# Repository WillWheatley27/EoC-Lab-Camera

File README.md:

| Supported Targets | ESP32 | ESP32-P4 | ESP32-S3 |
| ----------------- | ----- | -------- | -------- |

# ESP32-S3 SD + Mic + OV2640 Recorder

__WARNING:__ This project writes audio/video files to the SD card. Back up your data before testing.

Records:
- **Audio**: WAV via I2S mic (ICS-43434), `mic_0001.wav`, `mic_0002.wav`, ...
- **Video**: MJPEG via OV2640, `VID0001.MJP`, `VID0002.MJP`, ...

Core features:
- SDMMC FAT mount/unmount
- USB MSC to expose the SD card when idle
- SSD1306 I2C OLED status
- Button + buzzer UI
- BLE scan trigger (advertisements) with timestamped filenames

Supports SD (SDSC, SDHC, SDXC) cards and eMMC.

## Quick wiring map (ESP32-S3)

- **SD card:** GPIO4/5/6/7/15/16 (SDMMC)
- **Mic (I2S):** GPIO19/20/21
- **OLED (I2C):** GPIO41/42 (addr `0x3C`)
- **Camera (OV2640 SCCB):**
  - SCCB SDA: GPIO47
  - SCCB SCL: GPIO48
  - XCLK: GPIO3 (10 MHz)
  - D0..D7: GPIO8, 9, 10, 11, 12, 13, 14, 17
  - PCLK: GPIO18
  - VSYNC: GPIO21
  - HREF: GPIO46
  - PWDN/RESET: tied in hardware (PWDN → GND, RESET → 3.3V)

## Hardware

This project targets ESP32-S3 and uses an SD card breakout or slot, an I2S mic, an SSD1306 OLED, and an OV2640 camera.

Although it is possible to connect an SD card breakout adapter, keep in mind that connections using breakout cables are often unreliable and have poor signal integrity. You may need to use lower clock frequency when working with SD card breakout adapters.

This project doesn't utilize card detect (CD) and write protect (WP) signals from SD card slot.

### Pin assignments for ESP32

On ESP32, SDMMC peripheral is connected to specific GPIO pins using the IO MUX. GPIO pins cannot be customized. Please see the table below for the pin connections.

When using an ESP-WROVER-KIT board, this example runs without any extra modifications required. Only an SD card needs to be inserted into the slot.

ESP32 pin     | SD card pin | Notes
--------------|-------------|------------
GPIO14 (MTMS) | CLK         | 10k pullup in SD mode
GPIO15 (MTDO) | CMD         | 10k pullup in SD mode
GPIO2         | D0          | 10k pullup in SD mode, pull low to go into download mode (see Note about GPIO2 below!)
GPIO4         | D1          | not used in 1-line SD mode; 10k pullup in 4-line SD mode
GPIO12 (MTDI) | D2          | not used in 1-line SD mode; 10k pullup in 4-line SD mode (see Note about GPIO12 below!)
GPIO13 (MTCK) | D3          | not used in 1-line SD mode, but card's D3 pin must have a 10k pullup

### Pin assignments for ESP32-S3 (current project)

On ESP32-S3, SDMMC peripheral is connected to GPIO pins using GPIO matrix. This allows arbitrary GPIOs to be used to connect an SD card. In this example, GPIOs can be configured in two ways:

1. Using menuconfig: Run `idf.py menuconfig` in the project directory and open "SD/MMC Example Configuration" menu.
2. In the source code: See the initialization of `sdmmc_slot_config_t slot_config` structure in the example code.

The table below lists the default pin assignments.

When using an ESP32-S3-USB-OTG board, this example runs without any extra modifications required. Only an SD card needs to be inserted into the slot.

ESP32-S3 pin  | SD card pin | Notes
--------------|-------------|------------
GPIO4         | CLK         | 10k pullup
GPIO5         | CMD         | 10k pullup
GPIO6         | D0          | 10k pullup
GPIO7         | D1          | 10k pullup
GPIO15        | D2          | 10k pullup
GPIO16        | D3          | 10k pullup (required even in 1-line mode)

### I2S mic (ICS-43434)

ESP32-S3 pin  | Mic pin
--------------|---------
GPIO19        | BCLK/SCK
GPIO20        | WS/LRCL
GPIO21        | DOUT/SD
3.3V          | VCC
GND           | GND

SEL/LR on the mic should be tied to GND (left channel), which matches the code.

### OLED (SSD1306, I2C)

ESP32-S3 pin  | OLED pin
--------------|---------
GPIO41        | SDA
GPIO42        | SCL
3.3V          | VCC
GND           | GND

I2C address is `0x3C`.
Note: On ESP32-S3-DevKitC-1, GPIO41/42 are JTAG pins. Disable JTAG in `idf.py menuconfig` so they can be used for I2C.

### Camera (OV2640, Waveshare) — read this first

This project uses OV2640 over SCCB (I2C). The camera is sensitive to pin choice and initial frames are often corrupted.

**Working pin map (ESP32-S3):**

ESP32-S3 pin | OV2640 pin | Notes
-------------|------------|------
GPIO47       | SCCB SDA   | Camera I2C data
GPIO48       | SCCB SCL   | Camera I2C clock
GPIO3        | XCLK       | External clock (10 MHz)
GPIO8        | D0         | Data bit 0
GPIO9        | D1         | Data bit 1
GPIO10       | D2         | Data bit 2
GPIO11       | D3         | Data bit 3
GPIO12       | D4         | Data bit 4
GPIO13       | D5         | Data bit 5
GPIO14       | D6         | Data bit 6
GPIO17       | D7         | Data bit 7
GPIO18       | PCLK       | Pixel clock
GPIO21       | VSYNC      | Frame sync
GPIO46       | HREF       | Line sync

PWDN and RESET are tied in hardware (PWDN -> GND, RESET -> 3.3V). In software, they are disabled (set to `-1`).

**What was broken and how it was fixed:**

- SCCB was originally on GPIO36/37, which are used internally by Octal flash/PSRAM on ESP32-S3-WROOM-2, so SCCB traffic failed.
  Fix: move SCCB to GPIO47/48 and set `sccb_i2c_port = I2C_NUM_0`.
- OLED and camera shared an I2C bus, and we mixed old I2C driver with a driver_ng wrapper, causing a runtime abort.
  Fix: split buses (OLED on I2C1 GPIO41/42, camera SCCB on I2C0 GPIO47/48) and remove SCCB mutex usage.
- Early frames were corrupted (NO-SOI/NO-EOI) and were written to file.
  Fix: discard the first 10 frames after init and only write frames with valid SOI/EOI markers.
- FATFS without LFN rejected long filenames.
  Fix: use 8.3 filename `VID0001.MJP`.
- OLED writes could overlap between tasks and hang I2C.
  Fix: serialize OLED I2C writes with a mutex and remove SD warning OLED spam.

**Playback note:** `VIDxxxx.MJP` is a raw MJPEG stream (not a container). VLC can play it; for QuickTime, convert to AVI/MP4.

### BLE trigger and timestamped filenames

The device scans BLE advertisements and uses a UUID-encoded timestamp to name files:

- **Video:** `MMDDHHMM.MJP`
- **Audio:** `MMDDHHMM.WAV`

If no valid BLE timestamp is seen, it falls back to the index names:

- `VID0001.MJP`
- `mic_0001.wav`

**UUID format (128-bit):** `00000000-0000-0000-TT00-YYMMDDHHMMSS`

- Prefix is fixed: all zeroes (`00 00 00 00 00 00 00 00`)
- `TT` = `01` short press, `02` long press
- `YYMMDDHHMMSS` are BCD digits (base-10 nibbles)
- Filenames use `MMDDHHMM` to stay 8.3-safe

### Button + buzzer

ESP32-S3 pin  | Device
--------------|---------
GPIO1         | Button (pull-up input)
GPIO2         | Passive buzzer (PWM output)

### Pin assignments for ESP32-P4

On ESP32-P4, Slot 1 of the SDMMC peripheral is connected to GPIO pins using GPIO matrix. This allows arbitrary GPIOs to be used to connect an SD card. In this example, GPIOs can be configured in two ways:

1. Using menuconfig: Run `idf.py menuconfig` in the project directory and open `SD/MMC Example Configuration` menu.
2. In the source code: See the initialization of `sdmmc_slot_config_t slot_config` structure in the example code.

The table below lists the default pin assignments.

ESP32-P4 pin  | SD card pin | Notes
--------------|-------------|------------
GPIO43        | CLK         | 10k pullup
GPIO44        | CMD         | 10k pullup
GPIO39        | D0          | 10k pullup
GPIO40        | D1          | not used in 1-line SD mode; 10k pullup in 4-line mode
GPIO41        | D2          | not used in 1-line SD mode; 10k pullup in 4-line mode
GPIO42        | D3          | not used in 1-line SD mode, but card's D3 pin must have a 10k pullup

Default dedicated pins on ESP32-P4 are able to connect to an ultra high-speed SD card (UHS-I) which requires 1.8V switching (instead of the regular 3.3V). This means the user has to provide an external LDO power supply to use them, or to enable and configure an internal LDO via `idf.py menuconfig` -> `SD/MMC Example Configuration` -> `SD power supply comes from internal LDO IO`.

When using different GPIO pins this is not required and `SD power supply comes from internal LDO IO` setting can be disabled.

### 4-line and 1-line SD modes

By default, this example uses 4 line SD mode, utilizing 6 pins: CLK, CMD, D0 - D3. It is possible to use 1-line mode (CLK, CMD, D0) by changing "SD/MMC bus width" in the example configuration menu (see `CONFIG_EXAMPLE_SDMMC_BUS_WIDTH_1`).

Note that even if card's D3 line is not connected to the ESP chip, it still has to be pulled up, otherwise the card will go into SPI protocol mode.

### Note about GPIO2 (ESP32 only)

GPIO2 pin is used as a bootstrapping pin, and should be low to enter UART download mode. One way to do this is to connect GPIO0 and GPIO2 using a jumper, and then the auto-reset circuit on most development boards will pull GPIO2 low along with GPIO0, when entering download mode.

- Some boards have pulldown and/or LED on GPIO2. LED is usually ok, but pulldown will interfere with D0 signals and must be removed. Check the schematic of your development board for anything connected to GPIO2.

### Note about GPIO12 (ESP32 only)

GPIO12 is used as a bootstrapping pin to select output voltage of an internal regulator which powers the flash chip (VDD_SDIO). This pin has an internal pulldown so if left unconnected it will read low at reset (selecting default 3.3V operation). When adding a pullup to this pin for SD card operation, consider the following:

- For boards which don't use the internal regulator (VDD_SDIO) to power the flash, GPIO12 can be pulled high.
- For boards which use 1.8V flash chip, GPIO12 needs to be pulled high at reset. This is fully compatible with SD card operation.
- On boards which use the internal regulator and a 3.3V flash chip, GPIO12 must be low at reset. This is incompatible with SD card operation.
    * In most cases, external pullup can be omitted and an internal pullup can be enabled using a `gpio_pullup_en(GPIO_NUM_12);` call. Most SD cards work fine when an internal pullup on GPIO12 line is enabled. Note that if ESP32 experiences a power-on reset while the SD card is sending data, high level on GPIO12 can be latched into the bootstrapping register, and ESP32 will enter a boot loop until external reset with correct GPIO12 level is applied.
    * Another option is to burn the flash voltage selection efuses. This will permanently select 3.3V output voltage for the internal regulator, and GPIO12 will not be used as a bootstrapping pin. Then it is safe to connect a pullup resistor to GPIO12. This option is suggested for production use.

The following command can be used to program flash voltage selection efuses **to 3.3V**:

```sh
    espefuse.py set_flash_voltage 3.3V
```

This command will burn the `XPD_SDIO_TIEH`, `XPD_SDIO_FORCE`, and `XPD_SDIO_REG` efuses. With all three burned to value 1, the internal VDD_SDIO flash voltage regulator is permanently enabled at 3.3V. See the technical reference manual for more details.

`espefuse.py` has a `--do-not-confirm` option if running from an automated flashing script.

See [the document about pullup requirements](https://docs.espressif.com/projects/esp-idf/en/latest/api-reference/peripherals/sd_pullup_requirements.html) for more details about pullup support and compatibility of modules and development boards.

## How to use

### Build and flash

Build the project and flash it to the board, then run monitor tool to view serial output:

```
idf.py -p PORT flash monitor
```

(Replace PORT with serial port name.)

(To exit the serial monitor, type ``Ctrl-]``.)

### Recording flow

1. Long press starts recording. USB MSC is stopped and the SD card is mounted to the app.
2. Audio is written to `mic_0001.wav`, `mic_0002.wav`, etc.
3. Long press again stops recording, finalizes the WAV header, and returns the SD card to USB MSC.
4. A later long press repeats the cycle with a new filename.

Short press toggles pause/resume during recording. Each press produces a short beep.

### SD card mount warnings

If SD mounting fails or is not ready, the OLED shows a warning:

- `SD init failed`
- `SD mount failed`
- `SD not ready`

When these appear, re-seat the SD card and try again. Also wait for the
`Exposing SD card over USB` log before unplugging or copying files.

See the Getting Started Guide for full steps to configure and use ESP-IDF to build projects.

### USB mass storage

When idle, the SD card is exposed over USB MSC for file access from your computer.
During recording, USB MSC is stopped and the SD card is mounted to the application.
After recording finishes, USB MSC is restarted and the card is visible again on the host.

## Example output

Here is an example console output. In this case a 128MB SDSC card was connected, and `EXAMPLE_FORMAT_IF_MOUNT_FAILED` menuconfig option enabled. Card was unformatted, so the initial mount has failed. Card was then partitioned, formatted, and mounted again.

```
I (336) example: Initializing SD card
I (336) example: Using SDMMC peripheral
I (420) example: Mounting filesystem
I (538) mic: Waiting for long press
I (1840) button: Recording started
I (1841) mic: Recording started
I (9620) mic: Stop requested
I (9622) mic: Captured 7 sec to /sdcard/mic_0001.wav
I (9660) example: Card unmounted
```

## Troubleshooting

### Failure to download the example

```
Connecting........_____....._____....._____....._____....._____....._____....._____

A fatal error occurred: Failed to connect to Espressif device: Invalid head of packet (0x34)
```

Disconnect the SD card D0/MISO line from GPIO2 and try uploading again. Read "Note about GPIO2" above.

### Card fails to initialize with `sdmmc_init_sd_scr: send_scr (1) returned 0x107` error

Check connections between the card and the ESP32. For example, if you have disconnected GPIO2 to work around the flashing issue, connect it back and reset the ESP32 (using a button on the development board, or by pressing Ctrl-T Ctrl-R in IDF Monitor).

### Card fails to initialize with `sdmmc_check_scr: send_scr returned 0xffffffff` error

Connections between the card and the ESP32 are too long for the frequency used. Try using shorter connections, or try reducing the clock speed of SD interface.

### Failure to mount filesystem

```
example: Failed to mount filesystem. If you want the card to be formatted, set the EXAMPLE_FORMAT_IF_MOUNT_FAILED menuconfig option.
```
The example will be able to mount only cards formatted using FAT32 filesystem. If the card is formatted as exFAT or some other filesystem, you have an option to format it in the example code. Enable the `EXAMPLE_FORMAT_IF_MOUNT_FAILED` menuconfig option, then build and flash the example.

### Debug SD connections and pullup strength

> If the initialization of the SD card fails, initially follow the above options. If the issue persists, confirm the connection of pullups to the SD pins. To do this, enable the` Debug sd pin connections and pullup strength` option from menuconfig and rerun the code. This will provide the following result:

```
**** PIN recovery time ****

PIN 14 CLK  10044 cycles
PIN 15 CMD  10034 cycles
PIN  2  D0  10034 cycles
PIN  4  D1  10034 cycles
PIN 12  D2  10034 cycles
PIN 13  D3  10034 cycles

**** PIN recovery time with weak pullup ****

PIN 14 CLK  100 cycles
PIN 15 CMD  100 cycles
PIN  2  D0  100 cycles
PIN  4  D1  100 cycles
PIN 12  D2  100 cycles
PIN 13  D3  100 cycles

**** PIN voltage levels ****

PIN 14 CLK  0.6V
PIN 15 CMD  0.3V
PIN  2  D0  0.8V
PIN  4  D1  0.6V
PIN 12  D2  0.4V
PIN 13  D3  0.8V

**** PIN voltage levels with weak pullup ****

PIN 14 CLK  1.0V
PIN 15 CMD  1.1V
PIN  2  D0  1.0V
PIN  4  D1  1.0V
PIN 12  D2  1.0V
PIN 13  D3  1.2V

**** PIN cross-talk ****

              CLK   CMD    D0    D1    D2    D3
PIN 14 CLK     --   0.2V  0.1V  0.1V  0.1V  0.2V
PIN 15 CMD    0.1V   --   0.1V  0.1V  0.1V  0.1V
PIN  2  D0    0.1V  0.1V   --   0.2V  0.1V  0.1V
PIN  4  D1    0.1V  0.1V  0.3V   --   0.1V  0.1V
PIN 12  D2    0.1V  0.2V  0.2V  0.1V   --   0.1V
PIN 13  D3    0.1V  0.2V  0.1V  0.1V  0.1V   --

**** PIN cross-talk with weak pullup ****

              CLK   CMD    D0    D1    D2    D3
PIN 14 CLK     --   1.0V  1.0V  1.0V  1.0V  1.2V
PIN 15 CMD    0.9V   --   1.0V  1.0V  1.0V  1.2V
PIN  2  D0    0.9V  1.0V   --   1.0V  1.0V  1.2V
PIN  4  D1    0.9V  1.0V  1.2V   --   1.0V  1.2V
PIN 12  D2    0.9V  1.1V  1.2V  0.9V   --   1.2V
PIN 13  D3    0.9V  1.2V  1.1V  0.9V  0.9V   --
I (845) main_task: Returned from app_main()
```

In the absence of connected pullups and having the weak pullups enabled, you can assess the pullup connections by comparing PIN recovery time measured in CPU cycles. To check pullup connections, configure the pin as open drain, set it to low state, and count the cpu cycles consumed before returning to high state. If a pullup is connected, the pin will get back to high state after reasonably small cycle count, typically around 50-300 cycles, depending on pullup strength. If no pullup is connected, the PIN stays low and the measurement times out after 10000 cycles.

It will also provide the voltage levels at the corresponding SD pins. By default, this information is provided for ESP32 chip only, and for other chipsets, verify the availability of ADC pins for the respective GPIO using [this](https://docs.espressif.com/projects/esp-idf/en/latest/esp32/api-reference/peripherals/gpio.html#gpio-summary) and configure ADC mapped pins using menuconfig. Then test the voltage levels accordingly.

You can monitor the voltage levels of individual pins using `PIN voltage levels` and `PIN voltage levels with weak pullup`. However, if one pin being pulled low and experiencing interference with another pin, you can detect it through `PIN cross-talk` and `PIN cross-talk with weak pullup`. In the absence of pullups, voltage levels at each pin should range from 0 to 0.3V. With 10k pullups connected, the voltage will be between 3.1V to 3.3V, contingent on the connection between ADC pins and SD pins, and with weak pullups connected, it can fluctuate between 0.8V to 1.2V, depending on pullup strength.
>>>>>>> 207d2c1 (Initial commit)

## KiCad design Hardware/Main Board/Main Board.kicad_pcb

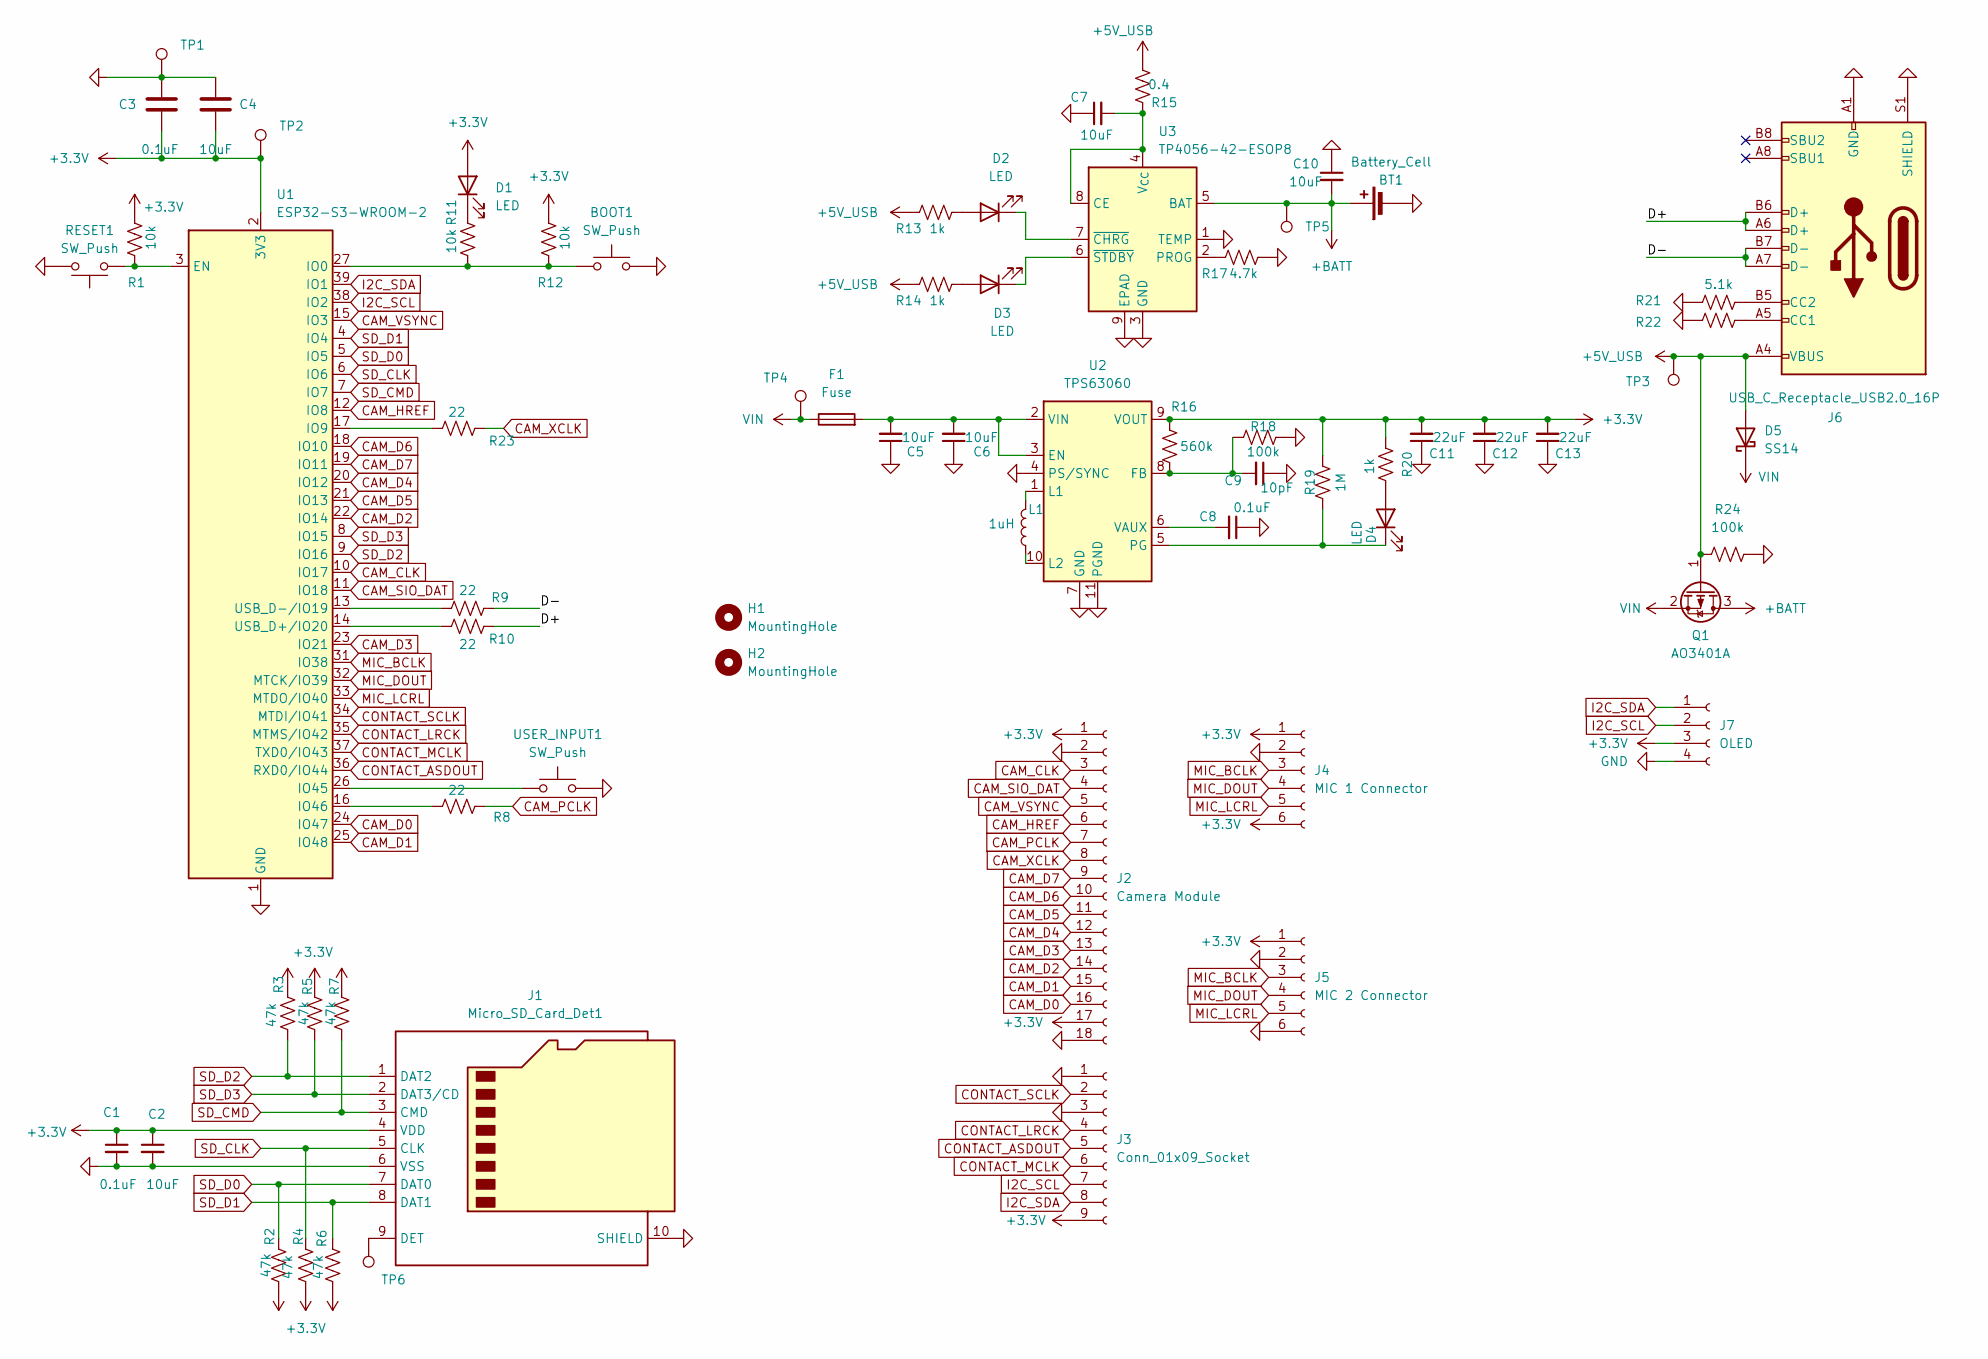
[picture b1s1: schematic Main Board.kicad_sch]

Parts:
BOOT1: SW_Push; SW_SPST_EVQP7A
BT1: Battery_Cell; JST_GH_SM02B-GHS-TB_1x02-1MP_P1.25mm_Horizontal
C1, C3, C8: 0.1uF; C_0402_1005Metric
C2, C7, C10: 10uF; C_0402_1005Metric
C4, C5, C6: 10uF; C_0603_1608Metric
C9: 10pF; C_0402_1005Metric
C11, C12, C13: 22uF; C_0805_2012Metric
D1, D2, D3, D4: LED; LED_0603_1608Metric
D5: SS14; D_SMA
F1: Fuse; Fuse_1206_3216Metric
H1, H2: MountingHole; MountingHole_2.1mm
J1: Micro_SD_Card_Det1; microSD_HC_Molex_104031-0811
J2: Camera Module; PinHeader_2x09_P2.54mm_Vertical
J3: Conn_01x09_Socket; JST_GH_SM09B-GHS-TB_1x09-1MP_P1.25mm_Horizontal
J4: MIC 1 Connector; JST_GH_SM06B-GHS-TB_1x06-1MP_P1.25mm_Horizontal
J5: MIC 2 Connector; JST_GH_SM06B-GHS-TB_1x06-1MP_P1.25mm_Horizontal
J6: USB_C_Receptacle_USB2.0_16P; USB_C_Receptacle_HRO_TYPE-C-31-M-12
J7: OLED; PinHeader_1x04_P2.54mm_Vertical
L1: 1uH; L_Bourns-SRN4018
Q1: AO3401A; SOT-23
R1, R11, R12: 10k; R_0402_1005Metric
R2, R3, R4, R5, R6, R7: 47k; R_0402_1005Metric
R8, R9, R10, R23: 22; R_0402_1005Metric
R13, R14, R20: 1k; R_0402_1005Metric
R15: 0.4; R_0402_1005Metric
R16: 560k; R_0402_1005Metric
R17: 4.7k; R_0402_1005Metric
R18, R24: 100k; R_0402_1005Metric
R19: 1M; R_0402_1005Metric
R21, R22: 5.1k; R_0402_1005Metric
RESET1: SW_Push; SW_SPST_EVQP7A
TP1, TP2, TP3: TestPoint; PinHeader_1x01_P2.54mm_Vertical
TP4, TP5, TP6: TestPoint; TestPoint_Pad_1.0x1.0mm
U1: ESP32-S3-WROOM-2
U2: TPS63060; Texas_S-PWSON-N10_ThermalVias
U3: TP4056-42-ESOP8; SOIC-8-1EP_3.9x4.9mm_P1.27mm_EP2.41x3.3mm_ThermalVias
USER_INPUT1: SW_Push; SW_SPST_PTS645

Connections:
+3.3V: C1.1, C2.1, C3.2, C4.1, C11.2, C12.2, C13.2, D1.2 (A), J1.4 (VDD), J2.1, J2.17, J3.9, J4.1, J4.6, J5.1, J7.3, R1.1, R2.1, R3.2, R4.1, R5.2, R6.1, R7.2, R12.1, R16.2, R19.2, R20.2, TP2.1, U1.2 (3V3), U2.9 (VOUT)
+5V_USB: D5.2 (A), J6.A4 (VBUS), J6.A9 (VBUS), J6.B4 (VBUS), J6.B9 (VBUS), Q1.1 (G), R13.2, R14.2, R15.1, R24.1, TP3.1
+BATT: BT1.1 (+), C10.2, Q1.3 (D), TP5.1, U3.5 (BAT)
/D+: J6.A6 (D+), J6.B6 (D+), R10.1
/D-: J6.A7 (D-), J6.B7 (D-), R9.1
CAM_CLK: J2.3, U1.10 (IO17)
CAM_D0: J2.16, U1.24 (IO47)
CAM_D1: J2.15, U1.25 (IO48)
CAM_D2: J2.14, U1.22 (IO14)
CAM_D3: J2.13, U1.23 (IO21)
CAM_D4: J2.12, U1.20 (IO12)
CAM_D5: J2.11, U1.21 (IO13)
CAM_D6: J2.10, U1.18 (IO10)
CAM_D7: J2.9, U1.19 (IO11)
CAM_HREF: J2.6, U1.12 (IO8)
CAM_PCLK: J2.7, R8.2
CAM_SIO_DAT: J2.4, U1.11 (IO18)
CAM_VSYNC: J2.5, U1.15 (IO3)
CAM_XCLK: J2.8, R23.2
CONTACT_ASDOUT: J3.5, U1.36 (RXD0/IO44)
CONTACT_LRCK: J3.4, U1.35 (MTMS/IO42)
CONTACT_MCLK: J3.6, U1.37 (TXD0/IO43)
CONTACT_SCLK: J3.2, U1.34 (MTDI/IO41)
GND: BOOT1.2, BT1.2 (-), C1.2, C2.2, C3.1, C4.2, C5.1, C6.1, C7.1, C8.1, C9.1, C10.1, C11.1, C12.1, C13.1, J1.6 (VSS), J1.10 (SHIELD), J2.2, J2.18, J3.1, J3.3, J4.2, J5.2, J5.6, J6.A1 (GND), J6.A12 (GND), J6.B1 (GND), J6.B12 (GND), J6.S1 (SHIELD), J7.4, R17.1, R18.1, R21.2, R22.2, R24.2, RESET1.2, TP1.1, U1.1 (GND), U1.40 (GND), U1.41 (GND), U2.4 (PS/SYNC), U2.7 (GND), U2.11 (PGND), U3.1 (TEMP), U3.3 (GND), U3.9 (EPAD), USER_INPUT1.2
I2C_SCL: J3.7, J7.2, U1.38 (IO2)
I2C_SDA: J3.8, J7.1, U1.39 (IO1)
MIC_BCLK: J4.3, J5.3, U1.31 (IO38)
MIC_DOUT: J4.4, J5.4, U1.32 (MTCK/IO39)
MIC_LCRL: J4.5, J5.5, U1.33 (MTDO/IO40)
unnamed: D1.1 (K), R11.2
unnamed: D2.2 (A), R13.1
unnamed: D2.1 (K), U3.7 (~CHRG)
unnamed: D3.2 (A), R14.1
unnamed: D3.1 (K), U3.6 (~STDBY)
unnamed: D4.2 (A), R20.1
unnamed: D4.1 (K), R19.1, U2.5 (PG)
unnamed: J1.9 (DET), TP6.1
unnamed: J6.A5 (CC1), R22.1
unnamed: J6.B5 (CC2), R21.1
unnamed: R1.2, RESET1.1, U1.3 (EN)
unnamed: BOOT1.1, R11.1, R12.2, U1.27 (IO0)
unnamed: R23.1, U1.17 (IO9)
unnamed: U1.26 (IO45), USER_INPUT1.1
unnamed: R8.1, U1.16 (IO46)
unnamed: R10.2, U1.14 (USB_D+/IO20)
unnamed: R9.2, U1.13 (USB_D-/IO19)
unnamed: C5.2, C6.2, F1.2, U2.2 (VIN), U2.3 (EN)
unnamed: C9.2, R16.1, R18.2, U2.8 (FB)
unnamed: L1.2, U2.1 (L1)
unnamed: L1.1, U2.10 (L2)
unnamed: C8.2, U2.6 (VAUX)
unnamed: C7.2, R15.2, U3.4 (V_{CC}), U3.8 (CE)
unnamed: R17.2, U3.2 (PROG)
SD_CLK: J1.5 (CLK), R4.2, U1.6 (IO6)
SD_CMD: J1.3 (CMD), R7.1, U1.7 (IO7)
SD_D0: J1.7 (DAT0), R2.2, U1.5 (IO5)
SD_D1: J1.8 (DAT1), R6.2, U1.4 (IO4)
SD_D2: J1.1 (DAT2), R3.1, U1.9 (IO16)
SD_D3: J1.2 (DAT3/CD), R5.1, U1.8 (IO15)
VIN: D5.1 (K), F1.1, Q1.2 (S), TP4.1

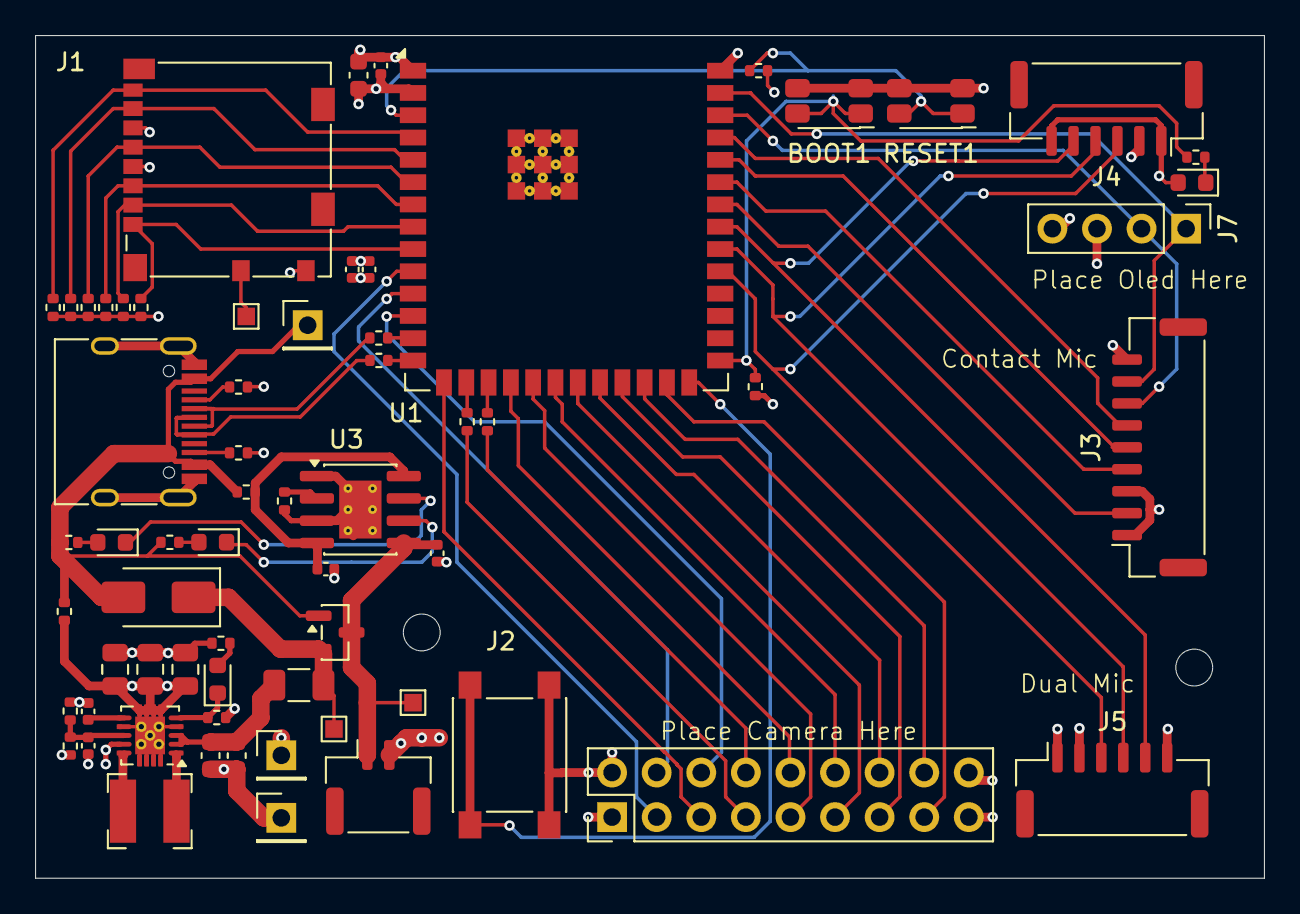
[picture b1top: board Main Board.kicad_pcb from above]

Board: 4 copper layers, 70.0 x 48.0 mm, 67 parts (0 on the bottom side), 60 nets.

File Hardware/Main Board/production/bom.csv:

Designator,Footprint,Quantity,Value,LCSC Part #
"BOOT1, RESET1",SW_SPST_EVQP7A,2,SW_Push,
BT1,JST_GH_SM02B-GHS-TB_1x02-1MP_P1.25mm_Horizontal,1,Battery_Cell,
"C1, C3, C8",0402,3,0.1uF,
"C10, C2, C7",0402,3,10uF,
"C11, C12, C13",0805,3,22uF,
"C4, C5, C6",0603,3,10uF,
C9,0402,1,10pF,
"D1, D2, D3, D4",0603,4,LED,
D5,D_SMA,1,SS14,
F1,1206,1,Fuse,
J1,microSD_HC_Molex_104031-0811,1,Micro_SD_Card_Det1,
J2,PinHeader_2x09_P2.54mm_Vertical,1,Camera Module,
J3,JST_GH_SM09B-GHS-TB_1x09-1MP_P1.25mm_Horizontal,1,Conn_01x09_Socket,
J4,JST_GH_SM06B-GHS-TB_1x06-1MP_P1.25mm_Horizontal,1,MIC 1 Connector,
J5,JST_GH_SM06B-GHS-TB_1x06-1MP_P1.25mm_Horizontal,1,MIC 2 Connector,
J6,USB_C_Receptacle_HRO_TYPE-C-31-M-12,1,USB_C_Receptacle_USB2.0_16P,
J7,PinHeader_1x04_P2.54mm_Vertical,1,OLED,
L1,L_Bourns-SRN4018,1,1uH,
Q1,SOT-23,1,AO3401A,
"R1, R11, R12",0402,3,10k,
"R10, R23, R8, R9",0402,4,22,
"R13, R14, R20",0402,3,1k,
R15,0402,1,0.4,
R16,0402,1,560k,
R17,0402,1,4.7k,
"R18, R24",0402,2,100k,
R19,0402,1,1M,
"R2, R3, R4, R5, R6, R7",0402,6,47k,
"R21, R22",0402,2,5.1k,
"TP1, TP2, TP3",PinHeader_1x01_P2.54mm_Vertical,3,TestPoint,
"TP4, TP5, TP6",TestPoint_Pad_1.0x1.0mm,3,TestPoint,
U1,ESP32-S3-WROOM-2,1,ESP32-S3-WROOM-2,
U2,Texas_S-PWSON-N10_ThermalVias,1,TPS63060,
U3,SOIC-8-1EP_3.9x4.9mm_P1.27mm_EP2.41x3.3mm_ThermalVias,1,TP4056-42-ESOP8,
USER_INPUT1,SW_SPST_PTS645,1,SW_Push,

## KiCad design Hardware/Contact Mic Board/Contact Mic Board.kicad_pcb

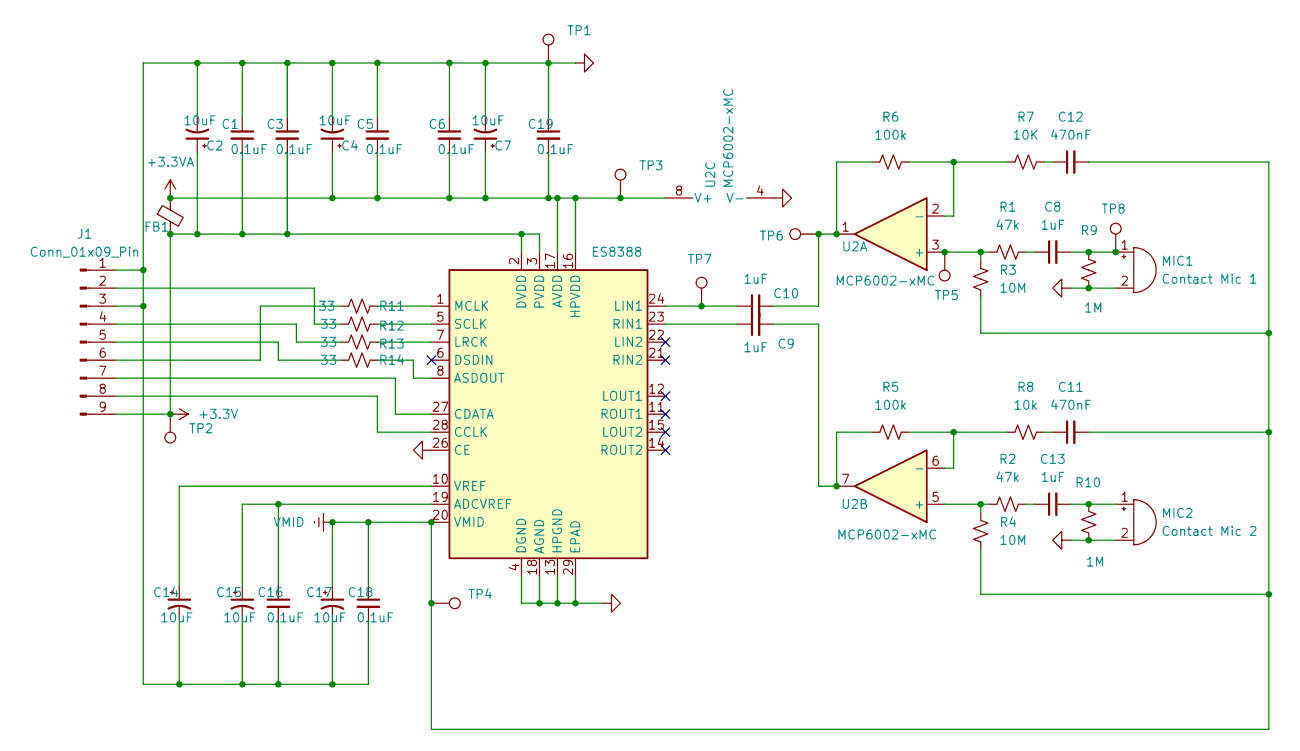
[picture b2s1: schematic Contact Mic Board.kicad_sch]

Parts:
C1, C3, C5, C6, C16, C18, C19: 0.1uF; C_0402_1005Metric
C2, C4, C7, C14, C15, C17: 10uF; C_0402_1005Metric
C8, C9, C10, C13: 1uF; C_0402_1005Metric
C11, C12: 470nF; C_0402_1005Metric
FB1: FerriteBead_Small; C_0603_1608Metric
J1: Conn_01x09_Pin; JST_GH_SM09B-GHS-TB_1x09-1MP_P1.25mm_Horizontal
MIC1: Contact Mic 1; PinHeader_1x02_P2.54mm_Vertical
MIC2: Contact Mic 2; PinHeader_1x02_P2.54mm_Vertical
R1, R2: 47k; C_0402_1005Metric
R3, R4: 10M; C_0402_1005Metric
R5, R6: 100k; D_0805_2012Metric_Pad1.15x1.40mm_HandSolder
R7: 10K; C_0402_1005Metric
R8: 10k; C_0402_1005Metric
R9, R10: 1M; C_0402_1005Metric
R11, R12, R13, R14: 33; C_0402_1005Metric
TP1, TP2, TP3, TP4, TP5, TP6, TP7, TP8: TestPoint; TestPoint_Pad_1.0x1.0mm
U1: ES8388; QFN-28-1EP_4x4mm_P0.45mm_EP2.6x2.6mm
U2: MCP6002-xMC; DFN-8-1EP_3x2mm_P0.5mm_EP1.75x1.45mm

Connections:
+3.3V: C1.2, C2.1, C3.2, FB1.2, J1.9, TP2.1, U1.2 (DVDD), U1.3 (PVDD)
+3.3VA: C4.1, C5.2, C6.2, C7.1, C19.2, FB1.1, TP3.1, U1.16 (HPVDD), U1.17 (AVDD), U2.8 (V+)
GND: C1.1, C2.2, C3.1, C4.2, C5.1, C6.1, C7.2, C14.2, C15.2, C16.2, C17.2, C18.2, C19.1, J1.1, J1.3, MIC1.2 (-), MIC2.2 (-), R9.2, R10.2, TP1.1, U1.4 (DGND), U1.13 (HPGND), U1.18 (AGND), U1.26 (CE), U1.29 (EPAD), U2.4 (V-), U2.9 (V-)
unnamed: C8.1, R1.2
unnamed: C9.2, R5.2, U2.7
unnamed: C10.2, R6.1, TP6.1, U2.1
unnamed: C11.1, R8.2
unnamed: C12.1, R7.2
unnamed: C13.1, R2.2
unnamed: J1.2, R12.1
unnamed: J1.4, R13.1
unnamed: J1.5, R14.1
unnamed: J1.6, R11.1
unnamed: J1.7, U1.27 (CDATA)
unnamed: J1.8, U1.28 (CCLK)
unnamed: C8.2, MIC1.1 (+), R9.1, TP8.1
unnamed: C13.2, MIC2.1 (+), R10.1
unnamed: C15.1, C16.1, U1.19 (ADCVREF)
unnamed: R14.2, U1.8 (ASDOUT)
unnamed: C10.1, TP7.1, U1.24 (LIN1)
unnamed: R13.2, U1.7 (LRCK)
unnamed: R11.2, U1.1 (MCLK)
unnamed: C9.1, U1.23 (RIN1)
unnamed: R12.2, U1.5 (SCLK)
unnamed: C14.1, U1.10 (VREF)
unnamed: R1.1, R3.1, TP5.1, U2.3 (+)
unnamed: R6.2, R7.1, U2.2 (-)
unnamed: R2.1, R4.1, U2.5 (+)
unnamed: R5.1, R8.1, U2.6 (-)
VMID: C11.2, C12.2, C17.1, C18.1, R3.2, R4.2, TP4.1, U1.20 (VMID)

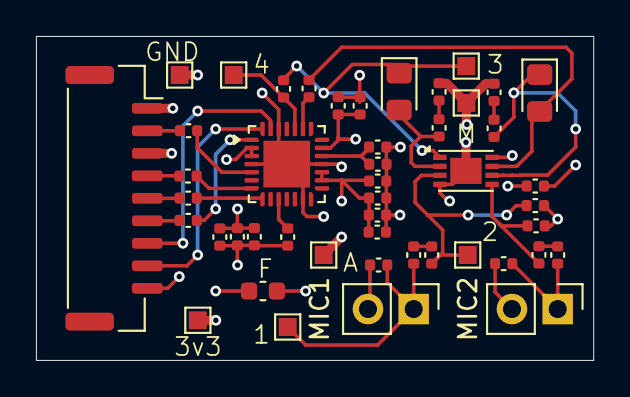
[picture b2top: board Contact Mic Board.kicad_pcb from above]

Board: 4 copper layers, 31.0 x 18.0 mm, 47 parts (0 on the bottom side), 30 nets.

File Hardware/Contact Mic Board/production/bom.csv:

Designator,Footprint,Quantity,Value,LCSC Part #
"C1, C16, C18, C19, C3, C5, C6",0402,7,0.1uF,
"C10, C13, C8, C9",0402,4,1uF,
"C11, C12",0402,2,470nF,
"C14, C15, C17, C2, C4, C7",0402,6,10uF,
FB1,0603,1,FerriteBead_Small,
J1,JST_GH_SM09B-GHS-TB_1x09-1MP_P1.25mm_Horizontal,1,Conn_01x09_Pin,
"R1, R2",0402,2,47k,
"R10, R9",0402,2,1M,
"R11, R12, R13, R14",0402,4,33,
"R3, R4",0402,2,10M,
"R5, R6",0805,2,100k,
"R7, R8",0402,2,10K,
U1,QFN-28-1EP_4x4mm_P0.45mm_EP2.6x2.6mm,1,ES8388,
U2,DFN-8-1EP_3x2mm_P0.5mm_EP1.75x1.45mm,1,MCP6002-xMC,

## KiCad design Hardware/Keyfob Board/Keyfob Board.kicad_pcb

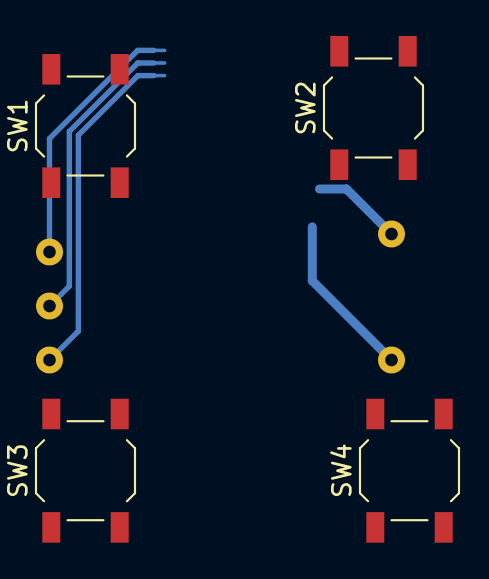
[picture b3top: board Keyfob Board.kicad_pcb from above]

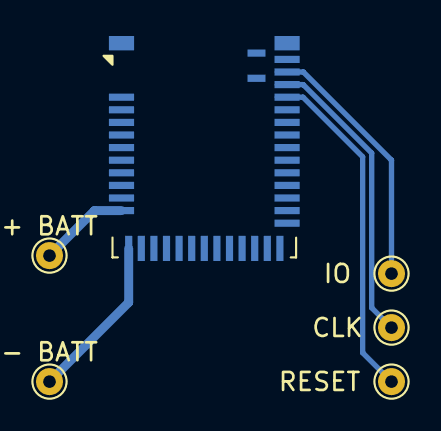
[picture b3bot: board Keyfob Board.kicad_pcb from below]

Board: 2 copper layers, 10 parts (6 on the bottom side), 9 nets.

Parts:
+ BATT: TestPoint; TestPoint_THTPad_D1.5mm_Drill0.7mm
- BATT: TestPoint; TestPoint_THTPad_D1.5mm_Drill0.7mm
CLK: TestPoint; TestPoint_THTPad_D1.5mm_Drill0.7mm
IO: TestPoint; TestPoint_THTPad_D1.5mm_Drill0.7mm
RESET: TestPoint; TestPoint_THTPad_D1.5mm_Drill0.7mm
SW1, SW2, SW3, SW4: SW_Push; SW_SPST_TL3342
U1: MDBT42Q-512K; Raytac_MDBT42Q

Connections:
+BATT: + BATT.1, U1.11 (VDD)
-BATT: - BATT.1, SW1.2, SW2.2, SW3.2, SW4.2, U1.1 (GND), U1.12 (GND), U1.24 (GND), U1.39 (GND)
unnamed: SW1.1, U1.25 (P0.11)
unnamed: SW2.1, U1.26 (P0.12)
unnamed: RESET.1, U1.35 (P0.21/~RESET)
unnamed: SW3.1, U1.40 (P0.24)
unnamed: SW4.1, U1.2 (P0.25)
unnamed: CLK.1, U1.36 (SWDCLK)
unnamed: IO.1, U1.37 (SWDIO)

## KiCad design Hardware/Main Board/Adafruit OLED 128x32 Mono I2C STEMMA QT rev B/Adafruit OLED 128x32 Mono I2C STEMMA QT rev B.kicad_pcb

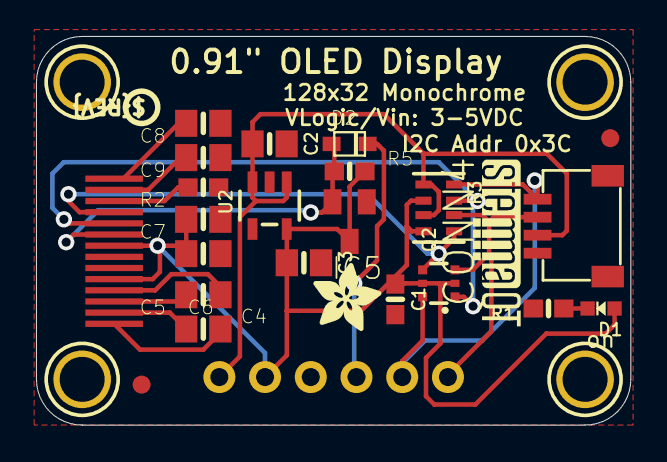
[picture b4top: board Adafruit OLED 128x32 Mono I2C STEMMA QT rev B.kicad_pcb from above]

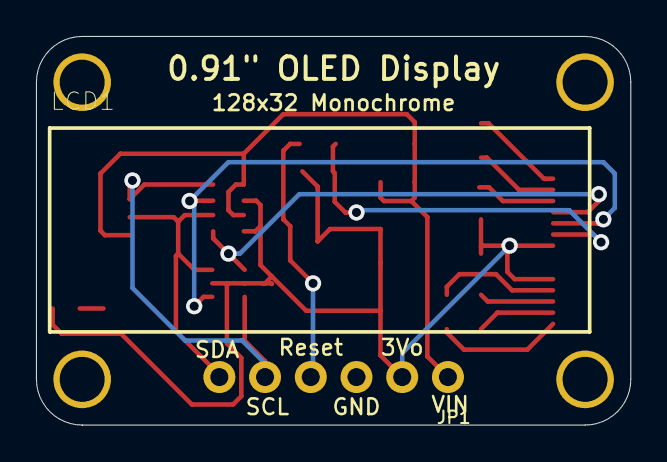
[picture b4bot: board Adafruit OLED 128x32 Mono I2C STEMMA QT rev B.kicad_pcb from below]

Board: 2 copper layers, 33.0 x 21.6 mm, 30 parts (2 on the bottom side), 17 nets.

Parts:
C1: 0.1uF; 0603-NO
C2, C3, C8, C9: 10uF; 0805-NO
C4, C5, C6, C7: 1uF; 0805-NO
CONN4: STEMMA_I2C_QT; JST_SH4
D1: GREEN; CHIPLED_0603_NOOUTLINE
D2: 1N4148; SOD-323F
FID3, FID4: FIDUCIAL_1MM
IC5: APX803; SOT23
JP1: 1X06_ROUND_70
LCD1: UG-2832HSWEG02_WRAPUNDER
Q2: BSS138; SOT363
R1, R5: 10K; 0603-NO
R2: 390K; 0603-NO
R3: 10K; RESPACK_4X0603
U2: AP2112K-3.3; SOT23-5
U$1, U$17, U$19, U$21: MOUNTINGHOLE2.5; MOUNTINGHOLE_2.5_PLATED
U$22: ADAFRUIT_3.5MM
U$25: PCBFEAT-REV-040
U$31: STEMMAQT

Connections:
3.3V: C1.1, C3.1, C6.2, C7.2, D1.A, IC5.3, JP1.2, LCD1.5, LCD1.8, Q2.2, Q2.5, R3.2, R3.4, R5.2, U2.5
GND: C1.2, C2.2, C3.2, C6.1, C7.1, C8.1, C9.1, CONN4.1, IC5.1, JP1.3, LCD1.7, R1.2, R2.1, U2.2
unnamed: C4.2, LCD1.1
unnamed: D1.C, R1.1
unnamed: C4.1, LCD1.2
unnamed: C5.2, LCD1.3
unnamed: C5.1, LCD1.4
unnamed: C9.2, LCD1.13
unnamed: LCD1.12, R2.2
unnamed: C8.2, LCD1.14
RESET: D2.C, JP1.4
RES_3V: D2.A, IC5.2, LCD1.9, R5.1
SCL: CONN4.4, JP1.5, Q2.6, R3.8
SCL_3V: LCD1.10, Q2.1, R3.7
SDA: CONN4.3, JP1.6, Q2.3, R3.6
SDA_3V: LCD1.11, Q2.4, R3.5
VCC: C2.1, CONN4.2, JP1.1, R3.1, R3.3, U2.1, U2.3

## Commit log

2026-01-17 Fix formatting in README.md
2026-01-18 Basic Recording controlled by single button press. Start and stop recording, pause and unpause recording
2026-01-24 added buzzer, OLED display for logging, fixed i2s sound quality issue by changing gpio pins, and added multiple back to back recordings
2026-01-28 Added time during recording so users can see how long the recording fcurrently is
2026-01-31 added schematics
2026-01-31 changed camera pins
2026-02-01 board
2026-02-02 split camera/OLED I2C, stabilize OV2640 MJPEG capture, and harden SD/video file handling
2026-02-02 Updated README.md to include camera and cleaned it up
2026-02-02 Moved camera-related code into camera_ov2640.c, updated mic capture to its oown task, and added SD card mounting OLED error
2026-02-10 reviewed schematic
2026-02-10 added bluetooth control at the uuids 000...1 and 000...2 for short and long press
2026-02-10 Designed contact mic board schematic
2026-02-13 created keyfob board, cleaned up hardware folder
2026-02-14 revised contact mic board
2026-02-14 feat(cam/oled/ble/sd): stabilize OLED I2C, add BLE timestamps, set VGA
    Use I2C mutex for OLED writes and remove SD warning OLED updates
    Add BLE scan trigger and timestamped filenames for mic/video
    Fix frame size mapping and set default frame size to VGA
2026-02-15 SD card schematic
2026-02-15 Finally fit all components on the board!
2026-02-15 updated readme with BLE and OLED bug fixes
2026-02-15 reviewed main board work done by Kevin
2026-02-19 schematics for oled and mics
2026-02-19 oled
2026-02-20 drafted contact mic pcb layout
2026-02-20 reviewed main board
2026-02-21 Finalized layout for contact mic board
2026-02-23 separated the microphone onto its own schematic as we won't be designing it. Updated the contact mic board
2026-02-23 BLE triggering and time stamp bug fixes
2026-02-23 Added power management onto the main board schematic
2026-02-24 drafted entire main board schematic and assigned footprints
2026-02-26 drafted main board layout
2026-02-26 revised main board layout, rearranged around strapping pins, rererouted for noise
2026-03-02 reviewed most of main board, getting ready to finalize and prepare for manufacturing
2026-03-04 fixed sd card, checked manufacturing feasibility and cleaned up board layout
